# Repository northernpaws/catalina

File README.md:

> Rythm is now Catalina!

# Catalina

> ⚠️ This is still a large work-in-progress! A semi-working version (hardware and software) is estimated to be ready around March 2026.

Catalina is an embedded-first Rust ecosystem for building music and audio processing devices, with a primary focus on ARM Cortex MCUs as the end-target.

The ecosystem is comprised of:
 * A Rust crate providing a DSP and audio engine designed for embedded devices (heapless by default, small footprint).
   * Various composable interfaces for quickly prototyping new instruments.
   * Drivers for common audio codecs, SDRAM, etc.
   * Windows, MacOS, and Linux support for developing audio chains before flashing to hardware.
   * Future web interface for synth design, with WebUSB for direct device flashing.
 * Two base hardware modules designed for the engine:
   * **Mini** - small footprint with audio processing.
   * **Card** - larger footprint with audio processing, CV and sync.
 * Several module "carrier" boards:
   * Breadboard-compatible carrier with headers.
   * Protoboard-style carrier with an integrated module.
 * Potentially some future soldering kits.
 * A Rust BSP (Board cupport package) crate that makes it easy to get started with any modules or boards from the ecosystem.

## TODO

  * [ ] Finish Mini module revision 1.
  * [ ] Finish Card module revision 2.
  * [ ] Stable minor release of `engine`, with audio and synth basic building blocks.

# Engine

[**Visit on crates.io**](https://crates.io/crates/catalina)

`catalina-engine` is a set of embedded-first DSP and audio engine crates that can be quickly integrated into embedded projects as a dependency, or used standalone with the std library for audio application.

The engine crates are designed to be as modular as possible, so i.e. if you just need a couple oscillators, you can use the oscillator module without needed to depend on any other parts of the engine. This composability is designed to make building audio effects and instruments as intuitive as possible.

The engine supports both the `core` embedded and `std` runtimes, including support for common embedded loggers (`defmt`, `log`), embedded and std library `tracing`, `std` and `alloc` feature sets from underlying libraries, and more via crate feature flags.

> Note! As the engine is embedded-first, `no_std` is set by feature flags by default. You'll need to manually enable the `std` feature to toggle off the default `no_std` declaration. 

Our goal is to make the usage of the engine as seamless as possible across both embedded and non-embedded platforms, making prototyping designs on PC and in simulators, and then later transferring them to embedded device runtimes as easy as possible.

# Modules

> ⚠️ The modules and their associated boards are a large work-in-progress! Several designs are only half-complete or still in the planning stages.

The modules provides a set of small STM32-based boards that can be embedded into custom PCB designs, or used with a set of associated carrier boards.

These carrier boards include basic breadboard header breakouts, some module-integrated protoboard designs, and some options for carriers with a selection of [Molex PicoBlade Connectors](https://www.molex.com/en-us/products/connectors/wire-to-board-connectors/picoblade-connectors) for modular plug-and-play prototyping.

Also see furthur in the README for kits that are designed as self-assembled soldering kits that let you quickly get started creating guitar/effects pedals, and small synths and sequencers using the toolkit.

> ⚠️ The ecosystem's modules are **NOT** able to be used standalone, they only have fine-pitch [Hirose DF40C board-to-board connectors](https://www.hirose.com/en/product/document?clcode=&productname=&series=DF40&documenttype=Catalog&lang=en&documentid=en_DF40_CAT) - a carrier board is required to interface with them!
>
> See our upcoming carriers or soldering kits below for examples.

## Mini

|   |  |  |
|:---:|:---:|:---:|

> ⚠️ Mini is in active design, these images may be out of date.

**[Schematic Viewer](https://kicanvas.org/?github=https%3A%2F%2Fgithub.com%2Fnorthernpaws%2Fcatalina%2Ftree%2Fmain%2Fhardware%2Fboards%2Fmini%2Fv0.2)**

  * 480MHz ARM Cortex-M7 processor (STM32H750XBHx)
  * 32MB of 16-bit SDRAM for audio buffers
  * 16MB QSPI Flash for programs and settings
  * 24-bit Stereo Audio Codec with internal mixer
  * SDMMC 4-bit interface
  * 1 Hardware MIDI Endpoint (RX and TX)

The Mini is a 20mm x 40mm module, designed to have a similar footprint to an Arduino Nano to make it easy to fit in a variaty of small audio and music devices. The Mini also has a breadboard-compatible carrier that exposes 2 columns of breadboard pins on either side of the carrier on standard 5-5 breadboard column layouts.

The mini is ideal for applications that don't need a large amount of audio RAM and need to fit in a small footprint - such as a guitar/effects pedal, Altoids tin, or 2HP Eurorack modules similar to [Erica Synths' Pico series](https://www.ericasynths.lv/shop/eurorack-modules/by-series/pico-series/).

### TODO

  * ~~[ ] In Revision 3, see if we can switch to SDMMC2 to enable both QSPI 1 and 2 simultaneously to expose one over the connector.~~
  * [x] *Or connect PG6 (`QUADSPI_BK1_NCS`) to connector, connect QUADSPI1 to connector, and provide a bootloader toggle that allows the carrier to indicate it should use carrier select pin.*
  * [ ] Determine values of remaining unspecified resistors and capacitors.
  * [ ] Calculate ideal HSE oscillator for the STM32H750.
  * [ ] Finish BOM selection for crystal, some resistors and capacitors.
  * [ ] Hirose DF40 connectors are now not recommended for dual-connector use. Despite still working for it, I don't feel comfortable going against manufacture recommendations for reliability reasons. For revision 3 we need to change to a single connector, possibly by shifting the MCU and RAM up or down to make room for a longer connector at 90 degrees on the bottom.

### Revision History

 * v0.1 - Original design with a BGA201 package. Ran into too many trace tollerance issues on fan-out, so had to upgrade to the BGA265 package to have enough room to run traces between via-in-pads and to do dogbones.
 * v0.2 - Changed to BGA 265, but layout changes from the 201 to 265 made x32 SDRAM layout near impossible. Switched to a 16mx16 SDRAM instead, which should be sufficient for the Mini. 
 * v0.3 - Found possible alignment and tolerance issues with mating 2x Hirose DF40 connectors, so shifted the MCU and codec to change the dual connectors for a single high-density one. Used DF40-90DP to have sufficient pins available, and because the 90-pin is more widely available.

### Notes

 * Mini was originally designed with the BGA201 package, but the pitch was too fine for economic fabrication capabilities. Upgraded to BGA265 in revision 2 to fix routing constraints. 
 * The Mini's original design concept was using 16mx32 SDRAM, with 32-bit SDRAM being ideal for handling encoding of stereo 16-bit audio samples (one 32-bit byte per stereo sample). Ultimately there was not enough room for routing x32 SDRAM with STM32's non-standard memory interface ball out, so a compromise to use 16-bit instead was made to keep the mini at in our 20mm wide constraint. 

## Card

> ⚠️ The card module is only in the planning stage.

Everything from the Mini:

  * 480MHz ARM Cortex-M7 processor
  * QSPI Flash
  * Stereo Audio Codec
  * SDMMC 4-bit interface

Plus:

  * 64MB of 32-bit SDRAM (4 times the amount on the Mini!)
  * Eurorack CV inputs (amount TBD)
  * Eurorack CV outputs (amount TBD)
  * Eurorack Sync In/Out (amount TBD)

The Card module is larger then the Mini, about the size of a credit card. It also features a different board-to-board connector from the Mini, supporting much higher board-to-board distances allowing it to seat over top of higher components (i.e. 3.5mm audio sockets) then the Mini can.

The Card is designed for audio applications that need significantly more memory, and benefit from having 32-bit memory (such as faster access for stereo 16-bit samples), like hardware samplers. The Card also features an onboard bank of dynamic CV sink, input, and output drivers that allow it to function as a Eurorack module off-the-shelf, or with synths and sequencers that have control voltage sockets.

### TODO

  * [ ] Ensure we can route a full 16mx32 SDRAM in the Card footprint.
  * [ ] Research the best CV circuits we can use to support a large range of biasing and voltages (i.e. -12v to +12v).
  * [ ] After SDRAM routing, can we break the parallel interface out to a B2B connector? Could be useful for driving displays, or memory expension with additional chips.
  * [ ] Aim to break out one of the QSPI interfaces so carriers can add additional flash. One ideas is for Card carriers to have their own carrier-specific flash that the module can load when attached, so programs don't need to be reflashed if sharing a module across carriers.
  * [ ] Uses DF40TC for higher range of hight offset. Maximum of 7mm allows mounting the module over most 3.5mm and USB sockets. DF40TC(3.0)-50DP-0.4V(51) as base, with: DF40TC-##DS-0.4V(51)   = 4.5 (min), DF40TC(4.0)-##DS-0.4V(51)  = 7.0mm (max).

# Carriers

Carriers are breakout boards for the core modules that make them easy to prototype and work with, without needing to make a custom board for their dense board-to-board connectors. 

Some of the planned carriers are:

  * "Discovery" line that breaks the module's IO's out to standard breadboard compatible pin headers. Includes a USB-C port for device and host mode, contains an ARM Cortex programming header keyed for an IDC cable, and possibly an SD card. Includes the required electrolytic capacitors for the integrated headphone driver on the modules.
  * "Proto" line that has a protoboard layout with a socket for the module in the center, making it easy to not only prototype more stable circuits directly with the module, but also to unsocket and swap the module between multiple proto boards so you don't need to buy several for different projects.

And a couple other ideas that need to be planned out:
  * A carrier that breaks out the audio and MIDI lines as 3.5mm sockets, and IO on [Molex PicoBlade connectors](https://www.google.com/search?client=safari&rls=en&q=picoblade+connector&ie=UTF-8&oe=UTF-8) for rapid modular prototyping (maybe use the "Discovery" name for this one instead?). 

## TODO
  * FUSB303BTMX on discovery for USB-C support
  * Amphenol_12401610E4-2A or HRO_TYPE-C-31-M-12?

# Kits

The hardware ecosystem will also include several soldering kits that are currently in various stages of development:
 * **Mini Module**
   * **Guitar/Effects Pedal Kit** - PCB with several connectors for knobs and foot switches, includes some knob and footswitch options, a Mini module, and 
   * **Mini Synth Kit** - A carrier similar to the Korg Volca or Behringer Pro series with a capacitive keyboard, several knobs and buttons, and 3.5mm MIDI minijack. Comes with a few printed faceplates and a 3D printed case. Carrier sockets could be solderable in kit form.
   * **Mini Step Sequencer Kit** - A small step or drum sequencer design, similar to the Roland AIRA Compact or Elektron Model lineup. Buttons and knobs solderable for kit form.
   * **Mini Groovebox Kit** - Something similar to an Elektron Model or Novation Circuit series device. A 4x8 velocity pad grid (velostat?), several knobs, and some menu buttons.
 * **Card Module**
   * **Eurorack Module Kit** - A 4-8 HP (to be determined) Eurorack carrier sporting all the Card CV inputs and outputs as standard 3.5mm sockets, USB, 3.5mm MIDI Minijack and an SD card.
   * **Pro Synth Kit** - Similar to the Midi Synth Kit, but also sporting a display, more control, and 3.5mm CV sockets.
   * **Pro Step Sequencer Kit** - Something similar to an Elektron Digitakt, SEQTRAK, or Korg SQ-1 with 16-step buttons, a display, and some knobs.

Each of these kits will come with a board support package via a feature flag in the Rust crate. These board support packages will come with all the scaffolding necessary to quickly build a project around the boards, as well as several example projects. 

# Supporters

Thank you to the supporters that helped design and fund this project!

It would not have been possible for me to spend the time or funds on making this without their support.

 * [Rachel Mant (@dragonmux)](https://github.com/dragonmux)
 * [Aki (@lethalbit)](https://github.com/lethalbit)
 * [Luna Rabbit (@LunaUsagi)](https://lunarabbit.moe)
 * [Sludge (@SludgeGirl)](https://github.com/SludgeGirl)
 * [Esden (@esden)](https://github.com/esden)
 * [Miika (@nykseli)](https://github.com/Nykseli)
 * Freyja
 * [Mary Guillemard (@marysaka)](https://github.com/marysaka)
 * [3cats](https://tokilabs.co)

If you would like to support this project, see either my [GitHub Sponsors page](https://github.com/sponsors/northernpaws) or [Patreon](https://www.patreon.com/cw/Northernpaws).

Support includes access to exclusive Discord channels with sneak peaks and design discussions.

# License

The hardware and CAD components of this project are licensed under the CERN Open Hardware License v2.0. The particular of the CERN-OHL license (permissive, weakly reciprocal, strongly reciprocal) can very depending on the hardware component and should be checked on a per-component basis by finding the closest LICENSE file to it.

The software components of this project are under the MIT license.

Concepts, such as the pin arrangement of the high-density connectors on the modules is consided free and open to build on, especially if you're looking to make a carrier board or product!

`SPDX-License-Identifier: CERN-OHL-S-2.0 AND MIT`

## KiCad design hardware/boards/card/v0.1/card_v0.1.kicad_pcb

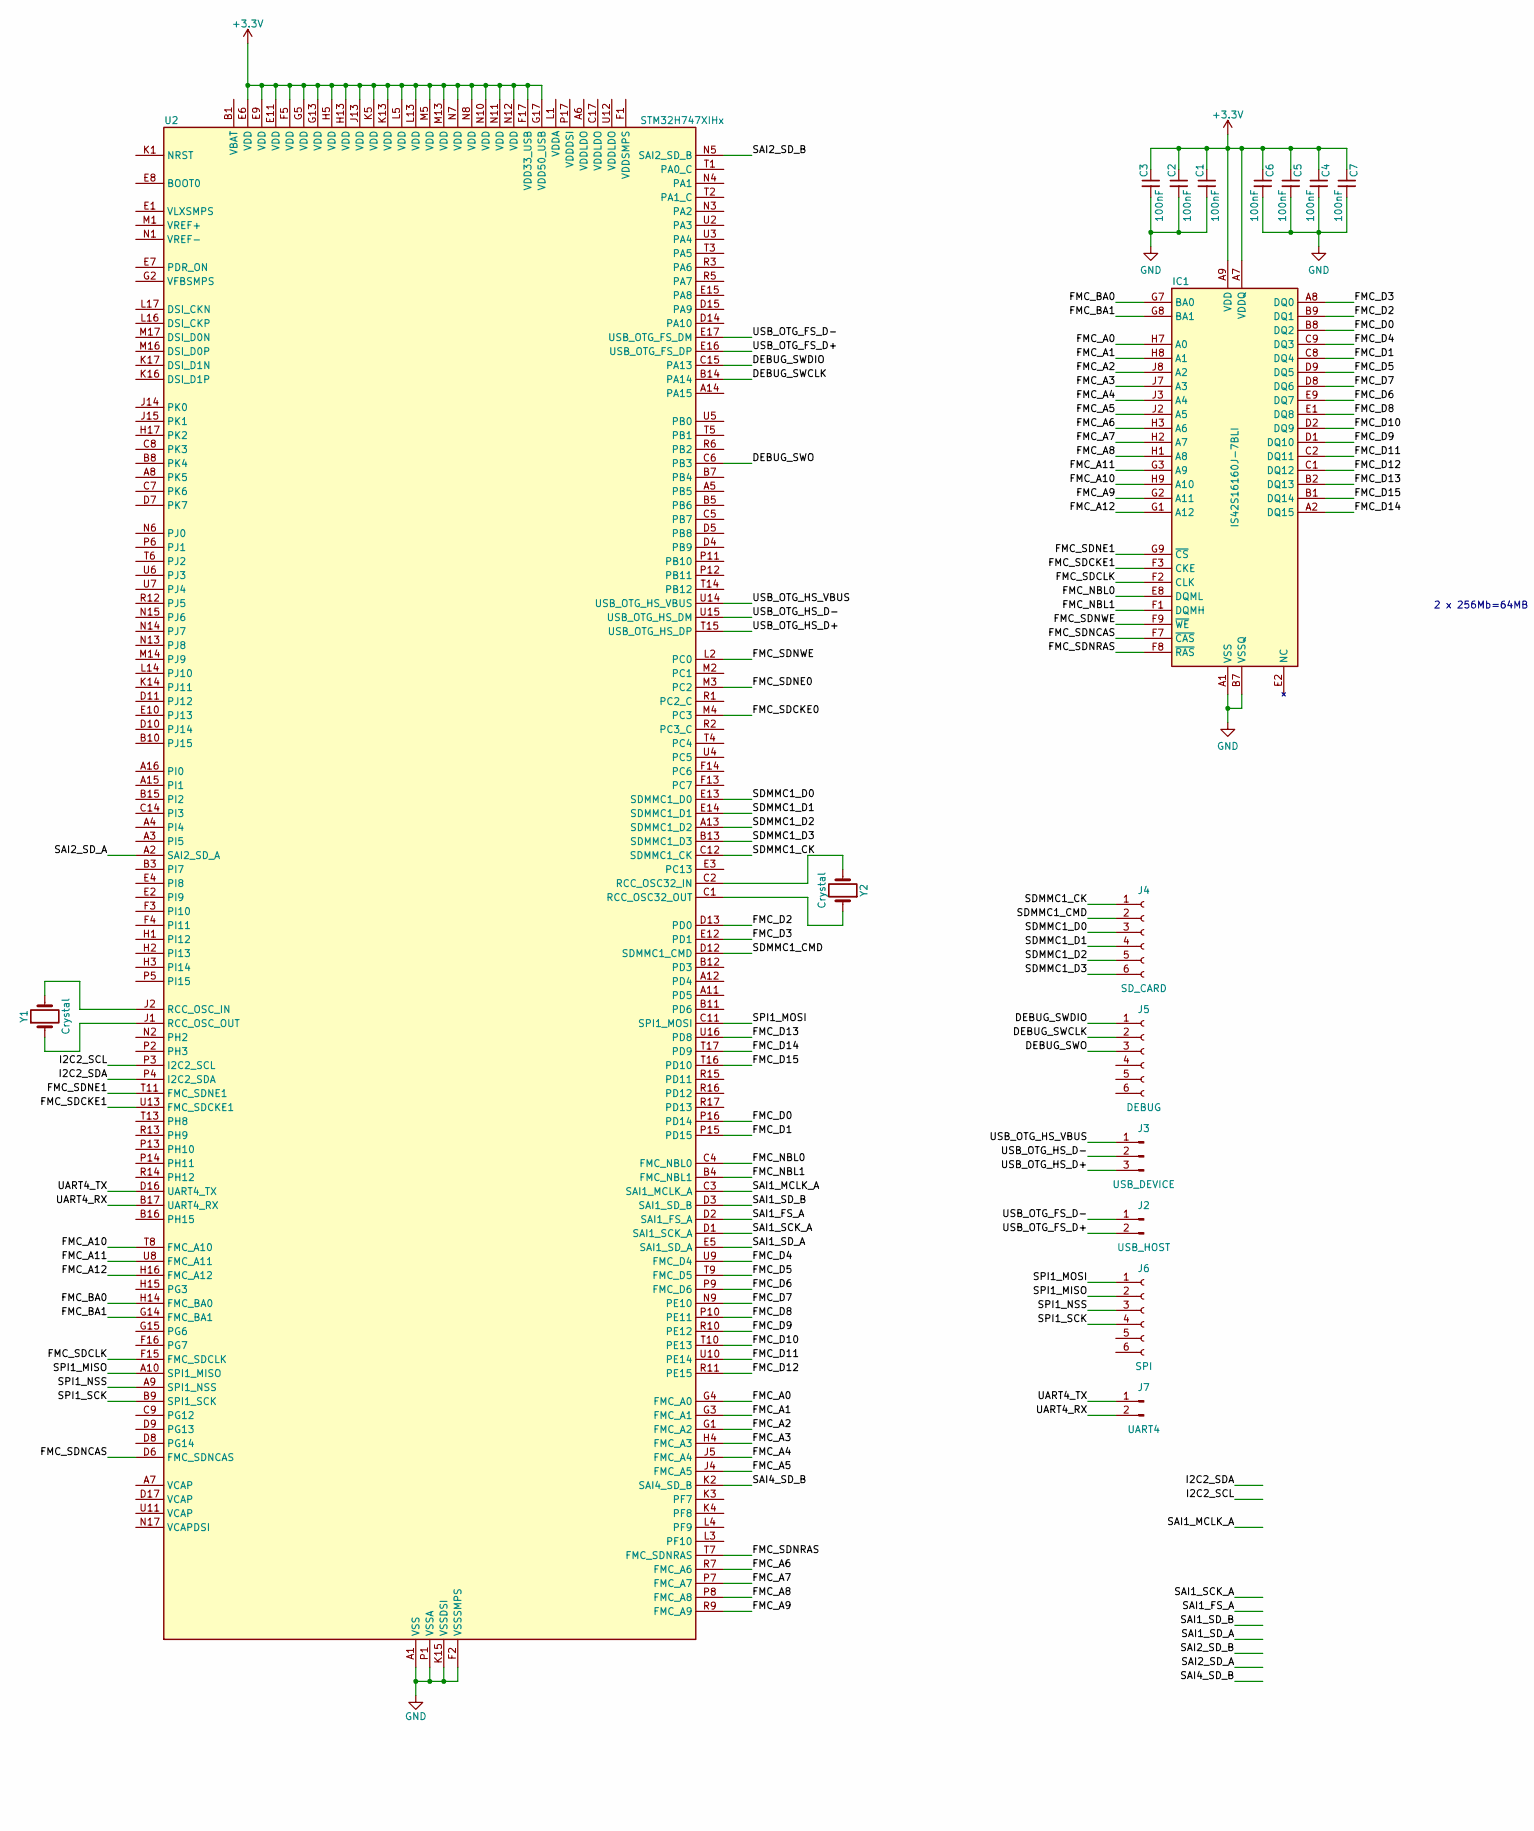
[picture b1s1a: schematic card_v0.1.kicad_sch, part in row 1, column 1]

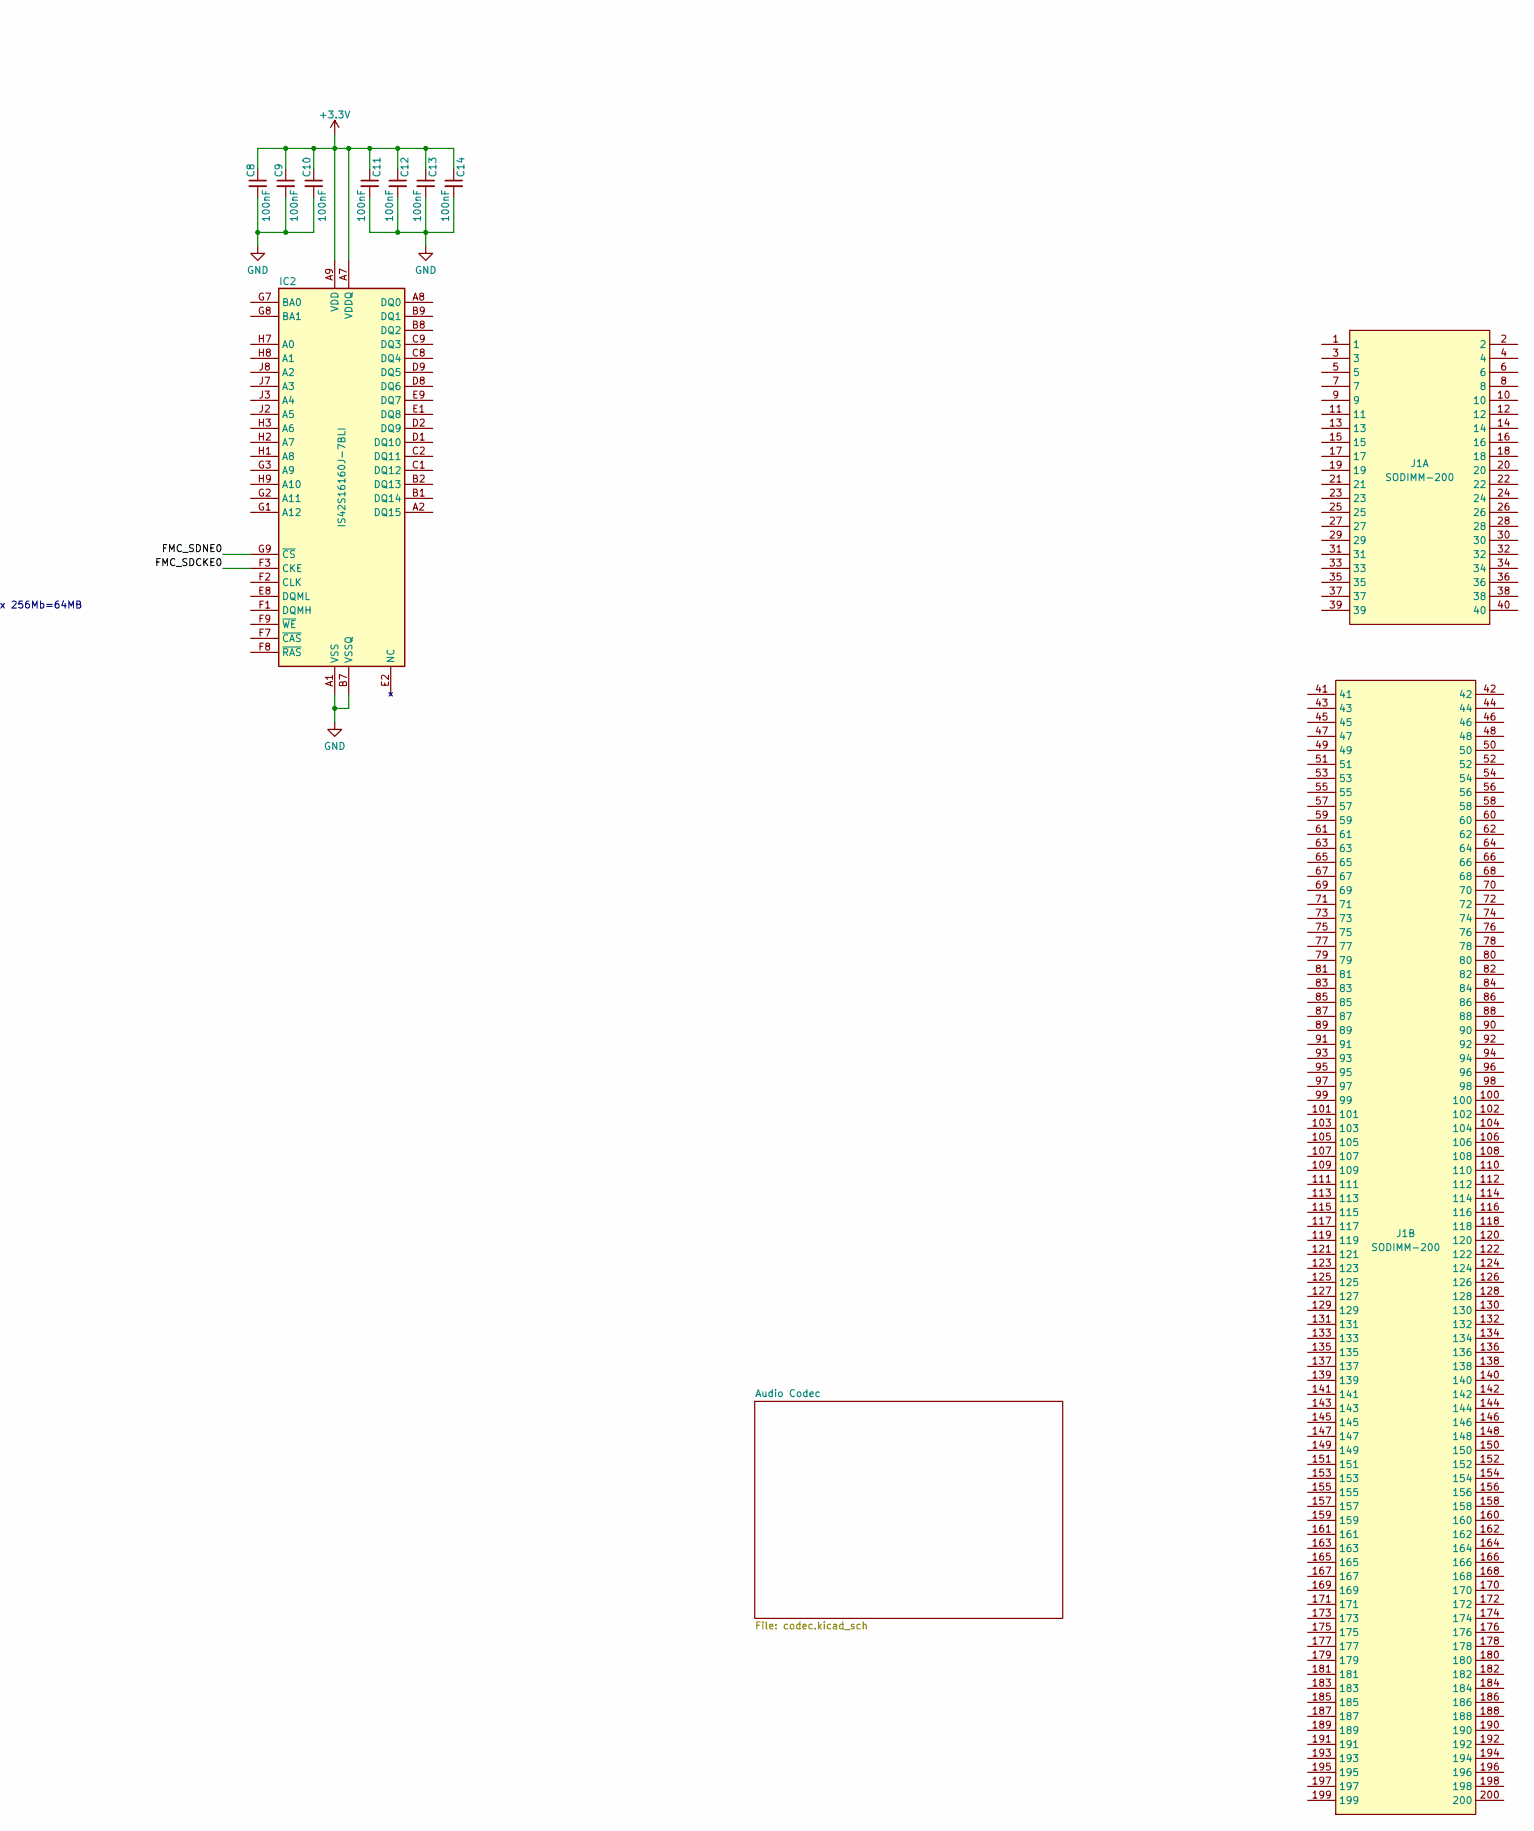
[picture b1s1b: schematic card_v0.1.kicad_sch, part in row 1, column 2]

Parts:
C1, C2, C3, C4, C5, C6, C7, C8, C9, C10, C11, C12, C13, C14: 100nF; C0402
IC1, IC2: IS42S16160J-7BLI; Mouser Part Number 870-42S16160J7BLI
J1: SODIMM-200; SODIMM-200_1.8V_Card_edge
J2: USB_HOST; PinHeader_1x02_P1.27mm_Vertical
J3: USB_DEVICE; PinHeader_1x03_P1.27mm_Vertical
J4: SD_CARD; PinHeader_1x06_P1.27mm_Vertical
J5: DEBUG; PinHeader_1x06_P1.27mm_Vertical
J6: SPI; PinHeader_1x06_P1.27mm_Vertical
J7: UART4; PinHeader_1x02_P1.27mm_Vertical
U2: STM32H747XIHx; TFBGA-265_14x14mm_Layout17x17_P0.8mm
Y1, Y2: Crystal; Crystal_SMD_3215-2Pin_3.2x1.5mm

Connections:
+3.3V: C1.1, C2.1, C3.1, C4.1, C5.1, C6.1, C7.1, C8.1, C9.1, C10.1, C11.1, C12.1, C13.1, C14.1, IC1.A7 (VDDQ), IC1.A9 (VDD), IC1.B3 (VDDQ), IC1.C7 (VDDQ), IC1.D3 (VDDQ), IC1.E7 (VDD), IC1.J9 (VDD), IC2.A7 (VDDQ), IC2.A9 (VDD), IC2.B3 (VDDQ), IC2.C7 (VDDQ), IC2.D3 (VDDQ), IC2.E7 (VDD), IC2.J9 (VDD), U2.E6 (VDD), U2.E9 (VDD), U2.E11 (VDD), U2.F5 (VDD), U2.F17 (VDD33_USB), U2.G5 (VDD), U2.G13 (VDD), U2.G17 (VDD50_USB), U2.H5 (VDD), U2.H13 (VDD), U2.J13 (VDD), U2.K5 (VDD), U2.K13 (VDD), U2.L5 (VDD), U2.L13 (VDD), U2.M5 (VDD), U2.M13 (VDD), U2.N7 (VDD), U2.N8 (VDD), U2.N10 (VDD), U2.N11 (VDD), U2.N12 (VDD); also elsewhere on the board
/DEBUG_SWCLK: J5.2, U2.B14 (PA14)
/DEBUG_SWDIO: J5.1, U2.C15 (PA13)
/DEBUG_SWO: J5.3, U2.C6 (PB3)
/FMC_A0: IC1.H7 (A0), U2.G4 (FMC_A0)
/FMC_A1: IC1.H8 (A1), U2.G3 (FMC_A1)
/FMC_A2: IC1.J8 (A2), U2.G1 (FMC_A2)
/FMC_A3: IC1.J7 (A3), U2.H4 (FMC_A3)
/FMC_A4: IC1.J3 (A4), U2.J5 (FMC_A4)
/FMC_A5: IC1.J2 (A5), U2.J4 (FMC_A5)
/FMC_A6: IC1.H3 (A6), U2.R7 (FMC_A6)
/FMC_A7: IC1.H2 (A7), U2.P7 (FMC_A7)
/FMC_A8: IC1.H1 (A8), U2.P8 (FMC_A8)
/FMC_A9: IC1.G2 (A11), U2.R9 (FMC_A9)
/FMC_A10: IC1.H9 (A10), U2.T8 (FMC_A10)
/FMC_A11: IC1.G3 (A9), U2.U8 (FMC_A11)
/FMC_A12: IC1.G1 (A12), U2.H16 (FMC_A12)
/FMC_BA0: IC1.G7 (BA0), U2.H14 (FMC_BA0)
/FMC_BA1: IC1.G8 (BA1), U2.G14 (FMC_BA1)
/FMC_D0: IC1.B8 (DQ2), U2.P16 (PD14)
/FMC_D1: IC1.C8 (DQ4), U2.P15 (PD15)
/FMC_D2: IC1.B9 (DQ1), U2.D13 (PD0)
/FMC_D3: IC1.A8 (DQ0), U2.E12 (PD1)
/FMC_D4: IC1.C9 (DQ3), U2.U9 (FMC_D4)
/FMC_D5: IC1.D9 (DQ5), U2.T9 (FMC_D5)
/FMC_D6: IC1.E9 (DQ7), U2.P9 (FMC_D6)
/FMC_D7: IC1.D8 (DQ6), U2.N9 (PE10)
/FMC_D8: IC1.E1 (DQ8), U2.P10 (PE11)
/FMC_D9: IC1.D1 (DQ10), U2.R10 (PE12)
/FMC_D10: IC1.D2 (DQ9), U2.T10 (PE13)
/FMC_D11: IC1.C2 (DQ11), U2.U10 (PE14)
/FMC_D12: IC1.C1 (DQ12), U2.R11 (PE15)
/FMC_D13: IC1.B2 (DQ13), U2.U16 (PD8)
/FMC_D14: IC1.A2 (DQ15), U2.T17 (PD9)
/FMC_D15: IC1.B1 (DQ14), U2.T16 (PD10)
/FMC_NBL0: IC1.E8 (DQML), U2.C4 (FMC_NBL0)
/FMC_NBL1: IC1.F1 (DQMH), U2.B4 (FMC_NBL1)
/FMC_SDCKE0: IC2.F3 (CKE), U2.M4 (PC3)
/FMC_SDCKE1: IC1.F3 (CKE), U2.U13 (FMC_SDCKE1)
/FMC_SDCLK: IC1.F2 (CLK), U2.F15 (FMC_SDCLK)
/FMC_SDNCAS: IC1.F7 (~CAS), U2.D6 (FMC_SDNCAS)
/FMC_SDNE0: IC2.G9 (~CS), U2.M3 (PC2)
/FMC_SDNE1: IC1.G9 (~CS), U2.T11 (FMC_SDNE1)
/FMC_SDNRAS: IC1.F8 (~RAS), U2.T7 (FMC_SDNRAS)
/FMC_SDNWE: IC1.F9 (~WE), U2.L2 (PC0)
/I2C2_SCL: U2.P3 (I2C2_SCL)
/I2C2_SDA: U2.P4 (I2C2_SDA)
/SAI1_FS_A: U2.D2 (SAI1_FS_A)
/SAI1_MCLK_A: U2.C3 (SAI1_MCLK_A)
/SAI1_SCK_A: U2.D1 (SAI1_SCK_A)
/SAI1_SD_A: U2.E5 (SAI1_SD_A)
/SAI1_SD_B: U2.D3 (SAI1_SD_B)
/SAI2_SD_A: U2.A2 (SAI2_SD_A)
/SAI2_SD_B: U2.N5 (SAI2_SD_B)
/SAI4_SD_B: U2.K2 (SAI4_SD_B)
/SDMMC1_CK: J4.1, U2.C12 (SDMMC1_CK)
/SDMMC1_CMD: J4.2, U2.D12 (SDMMC1_CMD)
/SDMMC1_D0: J4.3, U2.E13 (SDMMC1_D0)
/SDMMC1_D1: J4.4, U2.E14 (SDMMC1_D1)
/SDMMC1_D2: J4.5, U2.A13 (SDMMC1_D2)
/SDMMC1_D3: J4.6, U2.B13 (SDMMC1_D3)
/SPI1_MISO: J6.2, U2.A10 (SPI1_MISO)
/SPI1_MOSI: J6.1, U2.C11 (SPI1_MOSI)
/SPI1_NSS: J6.3, U2.A9 (SPI1_NSS)
/SPI1_SCK: J6.4, U2.B9 (SPI1_SCK)
/UART4_RX: J7.2, U2.B17 (UART4_RX)
/UART4_TX: J7.1, U2.D16 (UART4_TX)
/USB_OTG_FS_D+: J2.2, U2.E16 (USB_OTG_FS_DP)
/USB_OTG_FS_D-: J2.1, U2.E17 (USB_OTG_FS_DM)
/USB_OTG_HS_D+: J3.3, U2.T15 (USB_OTG_HS_DP)
/USB_OTG_HS_D-: J3.2, U2.U15 (USB_OTG_HS_DM)
/USB_OTG_HS_VBUS: J3.1, U2.U14 (USB_OTG_HS_VBUS)
GND: C1.2, C2.2, C3.2, C4.2, C5.2, C6.2, C7.2, C8.2, C9.2, C10.2, C11.2, C12.2, C13.2, C14.2, IC1.A1 (VSS), IC1.A3 (VSSQ), IC1.B7 (VSSQ), IC1.C3 (VSSQ), IC1.D7 (VSSQ), IC1.E3 (VSS), IC1.J1 (VSS), IC2.A1 (VSS), IC2.A3 (VSSQ), IC2.B7 (VSSQ), IC2.C3 (VSSQ), IC2.D7 (VSSQ), IC2.E3 (VSS), IC2.J1 (VSS), U2.A1 (VSS), U2.A17 (VSS), U2.B2 (VSS), U2.B6 (VSS), U2.C10 (VSS), U2.C13 (VSS), U2.C16 (VSS), U2.F2 (VSSSMPS), U2.G7 (VSS), U2.G8 (VSS), U2.G9 (VSS), U2.G10 (VSS), U2.G11 (VSS), U2.G16 (VSS), U2.H7 (VSS), U2.H8 (VSS), U2.H9 (VSS), U2.H10 (VSS), U2.H11 (VSS), U2.J3 (VSS), U2.J7 (VSS), U2.J8 (VSS), U2.J9 (VSS), U2.J10 (VSS), U2.J11 (VSS), U2.J16 (VSS), U2.J17 (VSS), U2.K7 (VSS), U2.K8 (VSS), U2.K9 (VSS), U2.K10 (VSS), U2.K11 (VSS), U2.K15 (VSSDSI), U2.L7 (VSS), U2.L8 (VSS), U2.L9 (VSS), U2.L10 (VSS), U2.L11 (VSS), U2.L15 (VSSDSI), U2.M15 (VSSDSI), U2.N16 (VSS), U2.P1 (VSSA), U2.R4 (VSS), U2.R8 (VSS), U2.T12 (VSS), U2.U1 (VSS), U2.U17 (VSS); also elsewhere on the board
unnamed: U2.C2 (RCC_OSC32_IN), Y2.2
unnamed: U2.C1 (RCC_OSC32_OUT), Y2.1
unnamed: U2.J2 (RCC_OSC_IN), Y1.2
unnamed: U2.J1 (RCC_OSC_OUT), Y1.1

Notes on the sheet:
2 x 256Mb=64MB

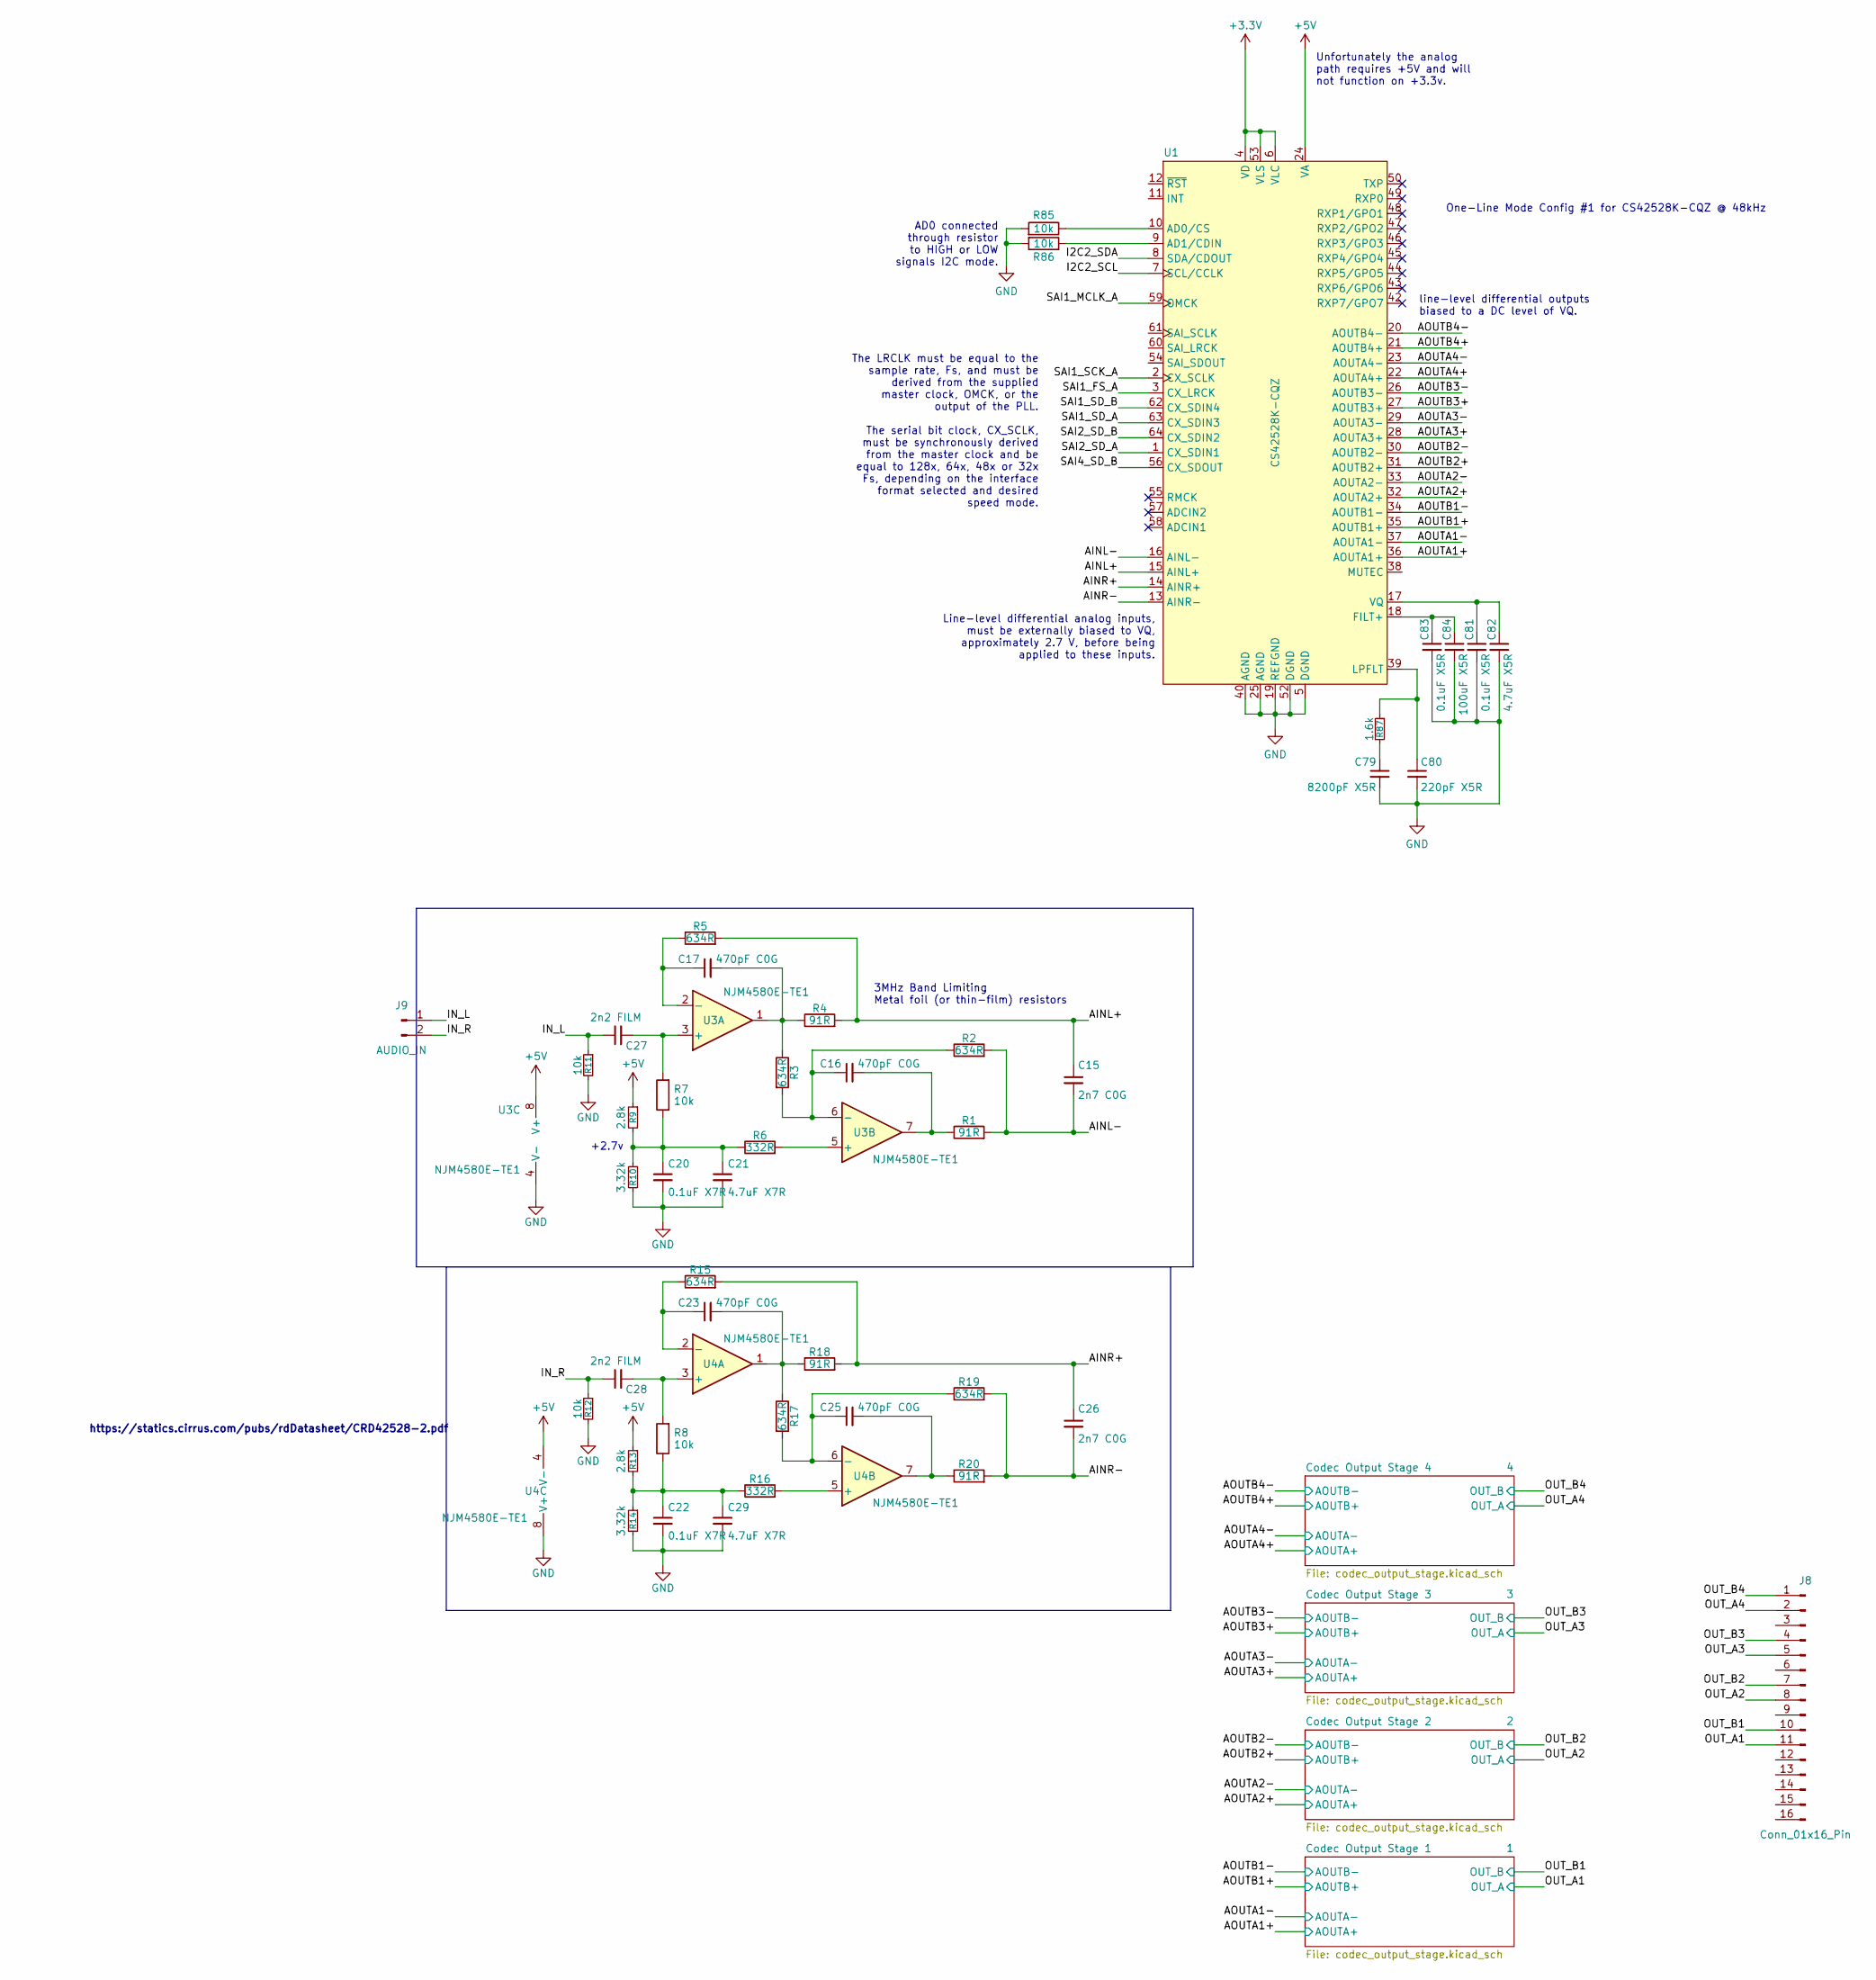
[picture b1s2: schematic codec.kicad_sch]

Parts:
C15, C26: 2n7 C0G; C0402
C16, C17, C23, C25: 470pF C0G; C0402
C20, C22: 0.1uF X7R; C0402
C21, C29: 4.7uF X7R; C0402
C27, C28: 2n2 FILM; C0603
C79: 8200pF X5R; C0402
C80: 220pF X5R; C0402
C81, C83: 0.1uF X5R; C0402
C82: 4.7uF X5R; C0402
C84: 100uF X5R; C0402
J8: Conn_01x16_Pin; PinHeader_1x16_P1.27mm_Vertical
J9: AUDIO_IN; PinHeader_1x02_P1.27mm_Vertical
R1, R4, R18, R20: 91R; R0402
R2, R3, R5, R15, R17, R19: 634R; R0402
R6, R16: 332R; R0402
R7, R8, R11, R12, R85, R86: 10k; R0402
R9, R13: 2.8k; R0402
R10, R14: 3.32k; R0402
R87: 1.6k; R0402
U1: CS42528K-CQZ; LQFP-64_10x10mm_P0.5mm
U3, U4: NJM4580E-TE1; TSSOP-8_3x3mm_P0.65mm

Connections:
+3.3V: U1.4 (VD), U1.6 (VLC), U1.51 (VD), U1.53 (VLS); also elsewhere on the board
+5V: R9.1, R13.1, U1.24 (VA), U1.41 (VA), U3.8 (V+), U4.4 (V-); also elsewhere on the board
/Audio Codec/AINL+: C15.1, R4.2, R5.2, U1.15 (AINL+)
/Audio Codec/AINL-: C15.2, R1.2, R2.2, U1.16 (AINL-)
/Audio Codec/AINR+: C26.1, R15.2, R18.2, U1.14 (AINR+)
/Audio Codec/AINR-: C26.2, R19.2, R20.2, U1.13 (AINR-)
/Audio Codec/AOUTA1+: U1.36 (AOUTA1+); also elsewhere on the board
/Audio Codec/AOUTA1-: U1.37 (AOUTA1-); also elsewhere on the board
/Audio Codec/AOUTA2+: U1.32 (AOUTA2+); also elsewhere on the board
/Audio Codec/AOUTA2-: U1.33 (AOUTA2-); also elsewhere on the board
/Audio Codec/AOUTA3+: U1.28 (AOUTA3+); also elsewhere on the board
/Audio Codec/AOUTA3-: U1.29 (AOUTA3-); also elsewhere on the board
/Audio Codec/AOUTA4+: U1.22 (AOUTA4+); also elsewhere on the board
/Audio Codec/AOUTA4-: U1.23 (AOUTA4-); also elsewhere on the board
/Audio Codec/AOUTB1+: U1.35 (AOUTB1+); also elsewhere on the board
/Audio Codec/AOUTB1-: U1.34 (AOUTB1-); also elsewhere on the board
/Audio Codec/AOUTB2+: U1.31 (AOUTB2+); also elsewhere on the board
/Audio Codec/AOUTB2-: U1.30 (AOUTB2-); also elsewhere on the board
/Audio Codec/AOUTB3+: U1.27 (AOUTB3+); also elsewhere on the board
/Audio Codec/AOUTB3-: U1.26 (AOUTB3-); also elsewhere on the board
/Audio Codec/AOUTB4+: U1.21 (AOUTB4+); also elsewhere on the board
/Audio Codec/AOUTB4-: U1.20 (AOUTB4-); also elsewhere on the board
/Audio Codec/I2C2_SCL: U1.7 (SCL/CCLK)
/Audio Codec/I2C2_SDA: U1.8 (SDA/CDOUT)
/Audio Codec/IN_L: C27.1, J9.1, R11.1
/Audio Codec/IN_R: C28.1, J9.2, R12.1
/Audio Codec/OUT_A1: J8.11; also elsewhere on the board
/Audio Codec/OUT_A2: J8.8; also elsewhere on the board
/Audio Codec/OUT_A3: J8.5; also elsewhere on the board
/Audio Codec/OUT_A4: J8.2; also elsewhere on the board
/Audio Codec/OUT_B1: J8.10; also elsewhere on the board
/Audio Codec/OUT_B2: J8.7; also elsewhere on the board
/Audio Codec/OUT_B3: J8.4; also elsewhere on the board
/Audio Codec/OUT_B4: J8.1; also elsewhere on the board
/Audio Codec/SAI1_FS_A: U1.3 (CX_LRCK)
/Audio Codec/SAI1_MCLK_A: U1.59 (OMCK)
/Audio Codec/SAI1_SCK_A: U1.2 (CX_SCLK)
/Audio Codec/SAI1_SD_A: U1.63 (CX_SDIN3)
/Audio Codec/SAI1_SD_B: U1.62 (CX_SDIN4)
/Audio Codec/SAI2_SD_A: U1.1 (CX_SDIN1)
/Audio Codec/SAI2_SD_B: U1.64 (CX_SDIN2)
/Audio Codec/SAI4_SD_B: U1.56 (CX_SDOUT)
GND: C20.2, C21.2, C22.2, C29.2, C79.2, C80.2, C81.2, C82.2, C83.2, C84.2, R10.2, R11.2, R12.2, R14.2, R85.2, R86.2, U1.5 (DGND), U1.19 (REFGND), U1.25 (AGND), U1.40 (AGND), U1.52 (DGND), U3.4 (V-), U4.8 (V+); also elsewhere on the board
unnamed: C16.2, R1.1, U3.7
unnamed: C17.2, R3.1, R4.1, U3.1
unnamed: C20.1, C21.1, R6.1, R7.1, R9.2, R10.1
unnamed: C22.1, C29.1, R8.1, R13.2, R14.1, R16.1
unnamed: C23.2, R17.1, R18.1, U4.1
unnamed: C25.2, R20.1, U4.7
unnamed: C79.1, R87.2
unnamed: R85.1, U1.10 (AD0/CS)
unnamed: R86.1, U1.9 (AD1/CDIN)
unnamed: C83.1, C84.1, U1.18 (FILT+)
unnamed: C80.1, R87.1, U1.39 (LPFLT)
unnamed: C81.1, C82.1, U1.17 (VQ)
unnamed: C27.2, R7.2, U3.3 (+)
unnamed: C17.1, R5.1, U3.2 (-)
unnamed: R6.2, U3.5 (+)
unnamed: C16.1, R2.1, R3.2, U3.6 (-)
unnamed: C28.2, R8.2, U4.3 (+)
unnamed: C23.1, R15.1, U4.2 (-)
unnamed: R16.2, U4.5 (+)
unnamed: C25.1, R17.2, R19.1, U4.6 (-)

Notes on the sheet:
AD0 connected through resistor to HIGH or LOW signals I2C mode.
Unfortunately the analog path requires +5V and will not function on +3.3v.
3MHz Band Limiting Metal foil (or thin-film) resistors
The LRCLK must be equal to the sample rate, Fs, and must be derived from the supplied master clock, OMCK, or the output of the PLL. The serial bit clock, CX_SCLK, must be synchronously derived from the master clock and be equal to 128x, 64x, 48x or 32x Fs, depending on the interface format selected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
+2.7v
line-level differential outputs biased to a DC level of VQ.
Line-level differential analog inputs, must be externally biased to VQ, approximately 2.7 V, before being applied to these inputs.
One-Line Mode Config #1 for CS42528K-CQZ @ 48kHz
https://statics.cirrus.com/pubs/rdDatasheet/CRD42528-2.pdf
